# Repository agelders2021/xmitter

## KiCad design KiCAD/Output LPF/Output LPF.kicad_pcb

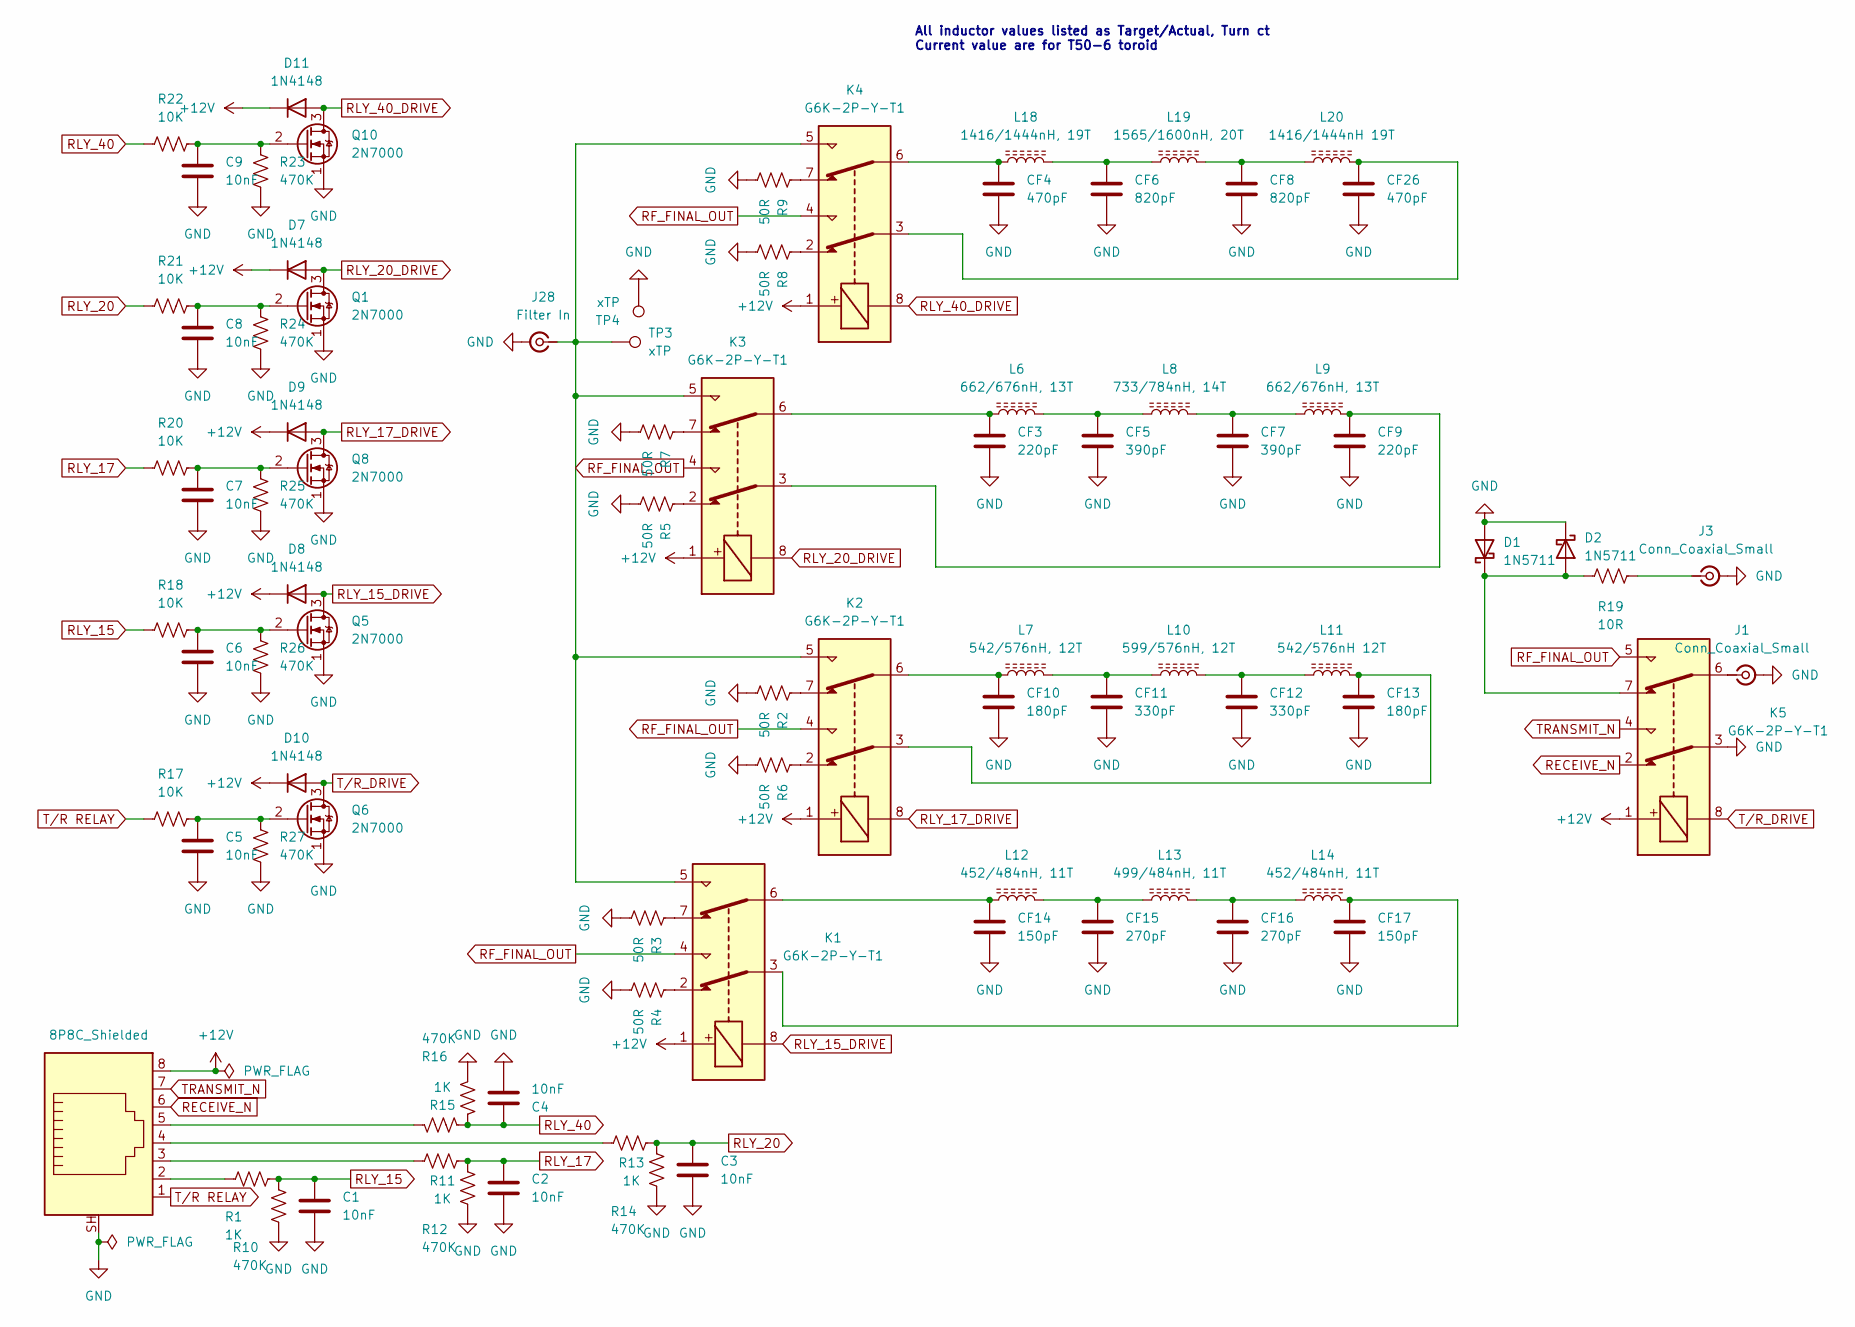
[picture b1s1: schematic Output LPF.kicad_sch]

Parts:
C1, C2, C3, C4, C5, C6, C7, C8, C9: 10nF; C_Disc_D6.0mm_W2.5mm_P5.00mm
CF3, CF9: 220pF; C_Disc_D7.5mm_W2.5mm_P5.00mm; Tolerance 1%
CF4, CF26: 470pF; C_Disc_D7.5mm_W2.5mm_P5.00mm; Tolerance 1%
CF5, CF7: 390pF; C_Disc_D7.5mm_W2.5mm_P5.00mm; Tolerance 1%
CF6, CF8: 820pF; C_Disc_D7.5mm_W2.5mm_P5.00mm; Tolerance 1%
CF10, CF13: 180pF; C_Disc_D7.5mm_W2.5mm_P5.00mm; Tolerance 1%
CF11, CF12: 330pF; C_Disc_D7.5mm_W2.5mm_P5.00mm; Tolerance 1%
CF14, CF17: 150pF; C_Disc_D7.5mm_W2.5mm_P5.00mm; Tolerance 1%
CF15, CF16: 270pF; C_Disc_D7.5mm_W2.5mm_P5.00mm; Tolerance 1%
D1, D2: 1N5711; D_DO-35_SOD27_P7.62mm_Horizontal
D7, D8, D9, D10, D11: 1N4148; D_DO-35_SOD27_P7.62mm_Horizontal
J1, J3: Conn_Coaxial_Small; SMA_Amphenol_132134_Vertical
J2: 8P8C_Shielded; Amphenol_RJE1D-188_Horizontal_Shielded
J28: Filter In; SMA_Amphenol_132134_Vertical
K1, K2, K3, K4, K5: G6K-2P-Y-T1; Relay_DPDT_G6K-2P-Y-T1
L6, L9: 662/676nH, 13T; T50-6_Vertical_HandWound
L7: 542/576nH, 12T; T50-6_Flat_HandWound
L8: 733/784nH, 14T; T50-6_Flat_HandWound
L10: 599/576nH, 12T; T50-6_Vertical_HandWound
L11: 542/576nH 12T; T50-6_Flat_HandWound
L12, L14: 452/484nH, 11T; T50-6_Flat_HandWound
L13: 499/484nH, 11T; T50-6_Vertical_HandWound
L18: 1416/1444nH, 19T; T50-6_Vertical_HandWound
L19: 1565/1600nH, 20T; T50-6_Flat_HandWound
L20: 1416/1444nH 19T; T50-6_Vertical_HandWound
Q1, Q5, Q6, Q8, Q10: 2N7000; TO-92_Inline
R1, R11, R13, R15: 1K; R_Axial_DIN0207_L6.3mm_D2.5mm_P10.16mm_Horizontal
R2, R3, R4, R5, R6, R7, R8, R9: 50R; R_Axial_DIN0207_L6.3mm_D2.5mm_P10.16mm_Horizontal
R10, R12, R14, R16, R23, R24, R25, R26, R27: 470K; R_Axial_DIN0207_L6.3mm_D2.5mm_P10.16mm_Horizontal
R17, R18, R20, R21, R22: 10K; R_Axial_DIN0207_L6.3mm_D2.5mm_P10.16mm_Horizontal
R19: 10R; R_Axial_DIN0207_L6.3mm_D2.5mm_P10.16mm_Horizontal
TP3, TP4: xTP; PinHeader_1x01_P2.54mm_Vertical

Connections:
+12V: D7.1 (K), D8.1 (K), D9.1 (K), D10.1 (K), D11.1 (K), J2.8, K1.1, K2.1, K3.1, K4.1, K5.1
GND: C1.2, C2.2, C3.2, C4.2, C5.2, C6.2, C7.2, C8.2, C9.2, CF3.2, CF4.2, CF5.2, CF6.2, CF7.2, CF8.2, CF9.2, CF10.2, CF11.2, CF12.2, CF13.2, CF14.2, CF15.2, CF16.2, CF17.2, CF26.2, D1.2 (A), D2.1 (K), J1.2 (Ext), J2.SH, J3.2 (Ext), J28.2 (Ext), K5.3, Q1.1 (S), Q5.1 (S), Q6.1 (S), Q8.1 (S), Q10.1 (S), R2.2, R3.2, R4.2, R5.2, R6.2, R7.2, R8.2, R9.2, R10.2, R12.2, R14.2, R16.2, R23.2, R24.2, R25.2, R26.2, R27.2, TP4.1 (1_1)
unnamed: CF3.1, K3.6, L6.1
unnamed: CF4.1, K4.6, L18.1
unnamed: CF5.1, L6.2, L8.1
unnamed: CF6.1, L18.2, L19.1
unnamed: CF7.1, L8.2, L9.1
unnamed: CF8.1, L19.2, L20.1
unnamed: CF9.1, K3.3, L9.2
unnamed: CF10.1, K2.6, L7.1
unnamed: CF11.1, L7.2, L10.1
unnamed: CF12.1, L10.2, L11.1
unnamed: CF13.1, K2.3, L11.2
unnamed: CF14.1, K1.6, L12.1
unnamed: CF15.1, L12.2, L13.1
unnamed: CF16.1, L13.2, L14.1
unnamed: CF17.1, K1.3, L14.2
unnamed: CF26.1, K4.3, L20.2
unnamed: D1.1 (K), D2.2 (A), K5.7, R19.1
unnamed: J1.1 (In), K5.6
unnamed: J2.2, R1.1
unnamed: J2.3, R11.1
unnamed: J2.4, R13.1
unnamed: J2.5, R15.1
unnamed: J3.1 (In), R19.2
unnamed: J28.1 (In), K1.5, K2.5, K3.5, K4.5, TP3.1 (1_1)
unnamed: K1.2, R4.1
unnamed: K1.7, R3.1
unnamed: K2.2, R6.1
unnamed: K2.7, R2.1
unnamed: K3.2, R5.1
unnamed: K3.7, R7.1
unnamed: K4.2, R8.1
unnamed: K4.7, R9.1
unnamed: C8.1, Q1.2 (G), R21.2, R24.1
unnamed: C6.1, Q5.2 (G), R18.2, R26.1
unnamed: C5.1, Q6.2 (G), R17.2, R27.1
unnamed: C7.1, Q8.2 (G), R20.2, R25.1
unnamed: C9.1, Q10.2 (G), R22.2, R23.1
RECEIVE_N: J2.6, K5.2
RF_FINAL_OUT: K1.4, K2.4, K3.4, K4.4, K5.5
RLY_15: C1.1, R1.2, R10.1, R18.1
RLY_15_DRIVE: D8.2 (A), K1.8, Q5.3 (D)
RLY_17: C2.1, R11.2, R12.1, R20.1
RLY_17_DRIVE: D9.2 (A), K2.8, Q8.3 (D)
RLY_20: C3.1, R13.2, R14.1, R21.1
RLY_20_DRIVE: D7.2 (A), K3.8, Q1.3 (D)
RLY_40: C4.1, R15.2, R16.1, R22.1
RLY_40_DRIVE: D11.2 (A), K4.8, Q10.3 (D)
TRANSMIT_N: J2.7, K5.4
T/R RELAY: J2.1, R17.1
T/R_DRIVE: D10.2 (A), K5.8, Q6.3 (D)

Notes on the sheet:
All inductor values listed as Target/Actual, Turn ct Current value are for T50-6 toroid

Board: 2 copper layers, 87 parts (0 on the bottom side), 52 nets, no tracks yet.

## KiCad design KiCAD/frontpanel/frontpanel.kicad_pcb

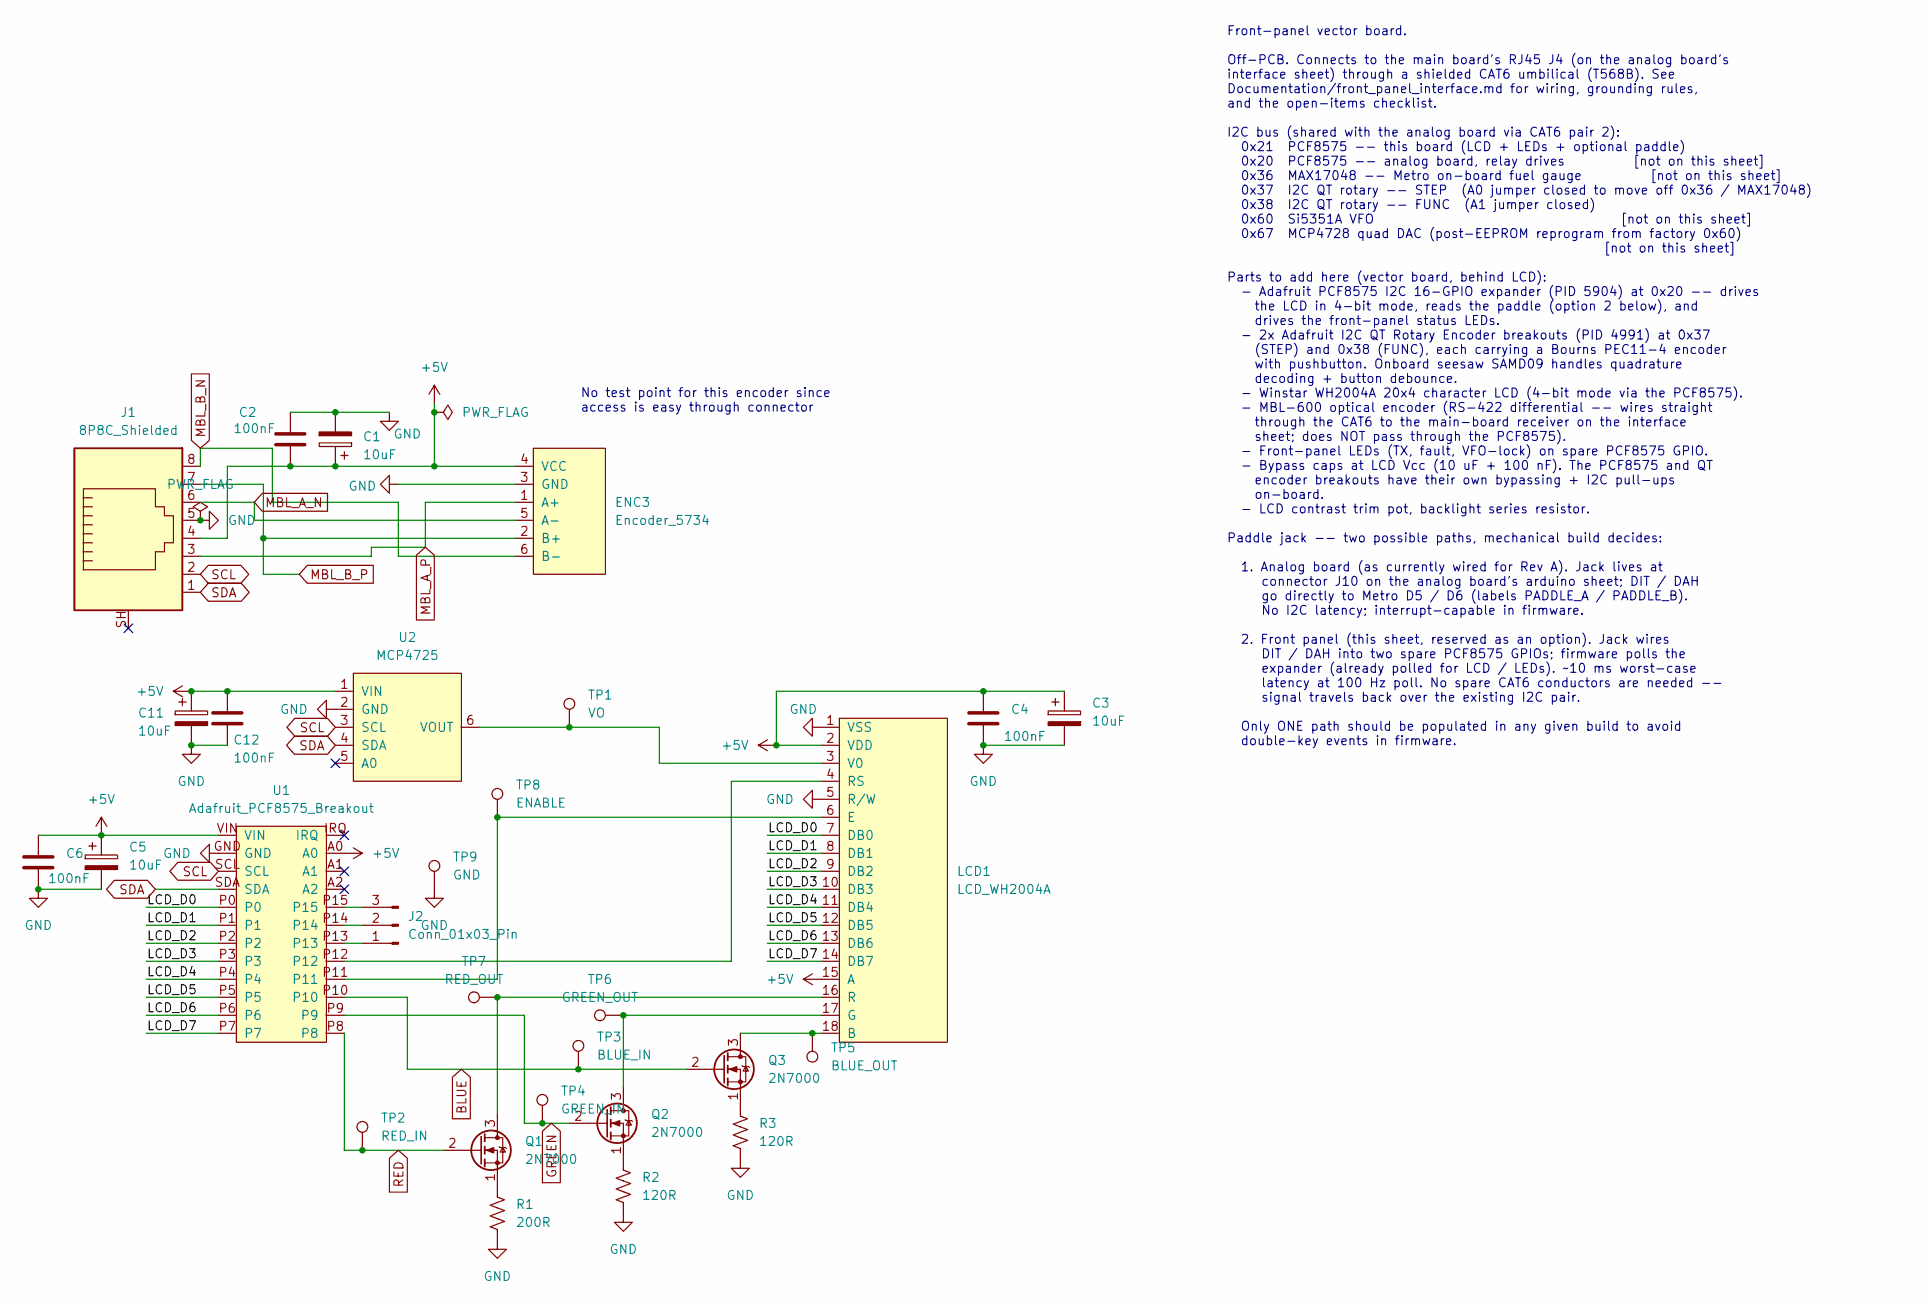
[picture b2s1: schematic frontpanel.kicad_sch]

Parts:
C1, C3, C5, C11: 10uF; CP_Radial_D5.0mm_P2.00mm
C2, C4, C6, C12: 100nF; C_Disc_D5.0mm_W2.5mm_P5.00mm
ENC3: Encoder_5734; PinHeader_1x06_P2.54mm_Vertical; MPN Adafruit #5734
J1: 8P8C_Shielded; Amphenol_RJE1D-188_Horizontal_Shielded
J2: Conn_01x03_Pin; PinHeader_1x03_P2.54mm_Vertical
LCD1: LCD_WH2004A; PinHeader_1x18_P2.54mm_Vertical; MPN WH2004A-CFH-JT# / Adafruit #498
Q1, Q2, Q3: 2N7000; TO-92_Inline
R1: 200R; R_Axial_DIN0207_L6.3mm_D2.5mm_P10.16mm_Horizontal
R2, R3: 120R; R_Axial_DIN0207_L6.3mm_D2.5mm_P10.16mm_Horizontal
TP1: VO; PinHeader_1x01_P2.54mm_Vertical
TP2: RED_IN; PinHeader_1x01_P2.54mm_Vertical
TP3: BLUE_IN; PinHeader_1x01_P2.54mm_Vertical
TP4: GREEN_IN; PinHeader_1x01_P2.54mm_Vertical
TP5: BLUE_OUT; PinHeader_1x01_P2.54mm_Vertical
TP6: GREEN_OUT; PinHeader_1x01_P2.54mm_Vertical
TP7: RED_OUT; PinHeader_1x01_P2.54mm_Vertical
TP8: ENABLE; PinHeader_1x01_P2.54mm_Vertical
TP9: GND; PinHeader_1x01_P2.54mm_Vertical
U1: Adafruit_PCF8575_Breakout; MPN Adafruit #5904
U2: MCP4725; Adafruit_MCP4725_Breakout; MPN Adafruit #935

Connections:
+5V: C1.1, C2.2, C3.1, C4.1, C5.1, C6.1, C11.1, C12.1, ENC3.4 (VCC), J1.4, LCD1.2 (VDD), LCD1.15 (A), U1.A0, U1.VIN, U2.1 (VIN)
/LCD_D0: LCD1.7 (DB0), U1.P0
/LCD_D1: LCD1.8 (DB1), U1.P1
/LCD_D2: LCD1.9 (DB2), U1.P2
/LCD_D3: LCD1.10 (DB3), U1.P3
/LCD_D4: LCD1.11 (DB4), U1.P4
/LCD_D5: LCD1.12 (DB5), U1.P5
/LCD_D6: LCD1.13 (DB6), U1.P6
/LCD_D7: LCD1.14 (DB7), U1.P7
BLUE: Q3.2 (G), TP3.1 (1_1), U1.P10
GND: C1.2, C2.1, C3.2, C4.2, C5.2, C6.2, C11.2, C12.2, ENC3.3 (GND), J1.5, LCD1.1 (VSS), LCD1.5 (R/W), R1.2, R2.2, R3.2, TP9.1 (1_1), U1.GND, U2.2 (GND)
GREEN: Q2.2 (G), TP4.1 (1_1), U1.P9
MBL_A_N: ENC3.5 (A-), J1.6
MBL_A_P: ENC3.1 (A+), J1.3
MBL_B_N: ENC3.6 (B-), J1.8
MBL_B_P: ENC3.2 (B+), J1.7
unnamed: J2.1, U1.P13
unnamed: J2.2, U1.P14
unnamed: J2.3, U1.P15
unnamed: LCD1.18 (B), Q3.3 (D), TP5.1 (1_1)
unnamed: LCD1.6 (E), TP8.1 (1_1), U1.P11
unnamed: LCD1.17 (G), Q2.3 (D), TP6.1 (1_1)
unnamed: LCD1.16 (R), Q1.3 (D), TP7.1 (1_1)
unnamed: LCD1.4 (RS), U1.P12
unnamed: LCD1.3 (V0), TP1.1 (1_1), U2.6 (VOUT)
unnamed: Q1.1 (S), R1.1
unnamed: Q2.1 (S), R2.1
unnamed: Q3.1 (S), R3.1
RED: Q1.2 (G), TP2.1 (1_1), U1.P8
SCL: J1.2, U1.SCL, U2.3 (SCL)
SDA: J1.1, U1.SDA, U2.4 (SDA)

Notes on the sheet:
Front-panel vector board. Off-PCB. Connects to the main board's RJ45 J4 (on the analog board's interface sheet) through a shielded CAT6 umbilical (T568B). See Documentation/front_panel_interface.md for wiring, grounding rules, and the open-items checklist. I2C bus (shared with the analog board via 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
No test point for this encoder since access is easy through connector

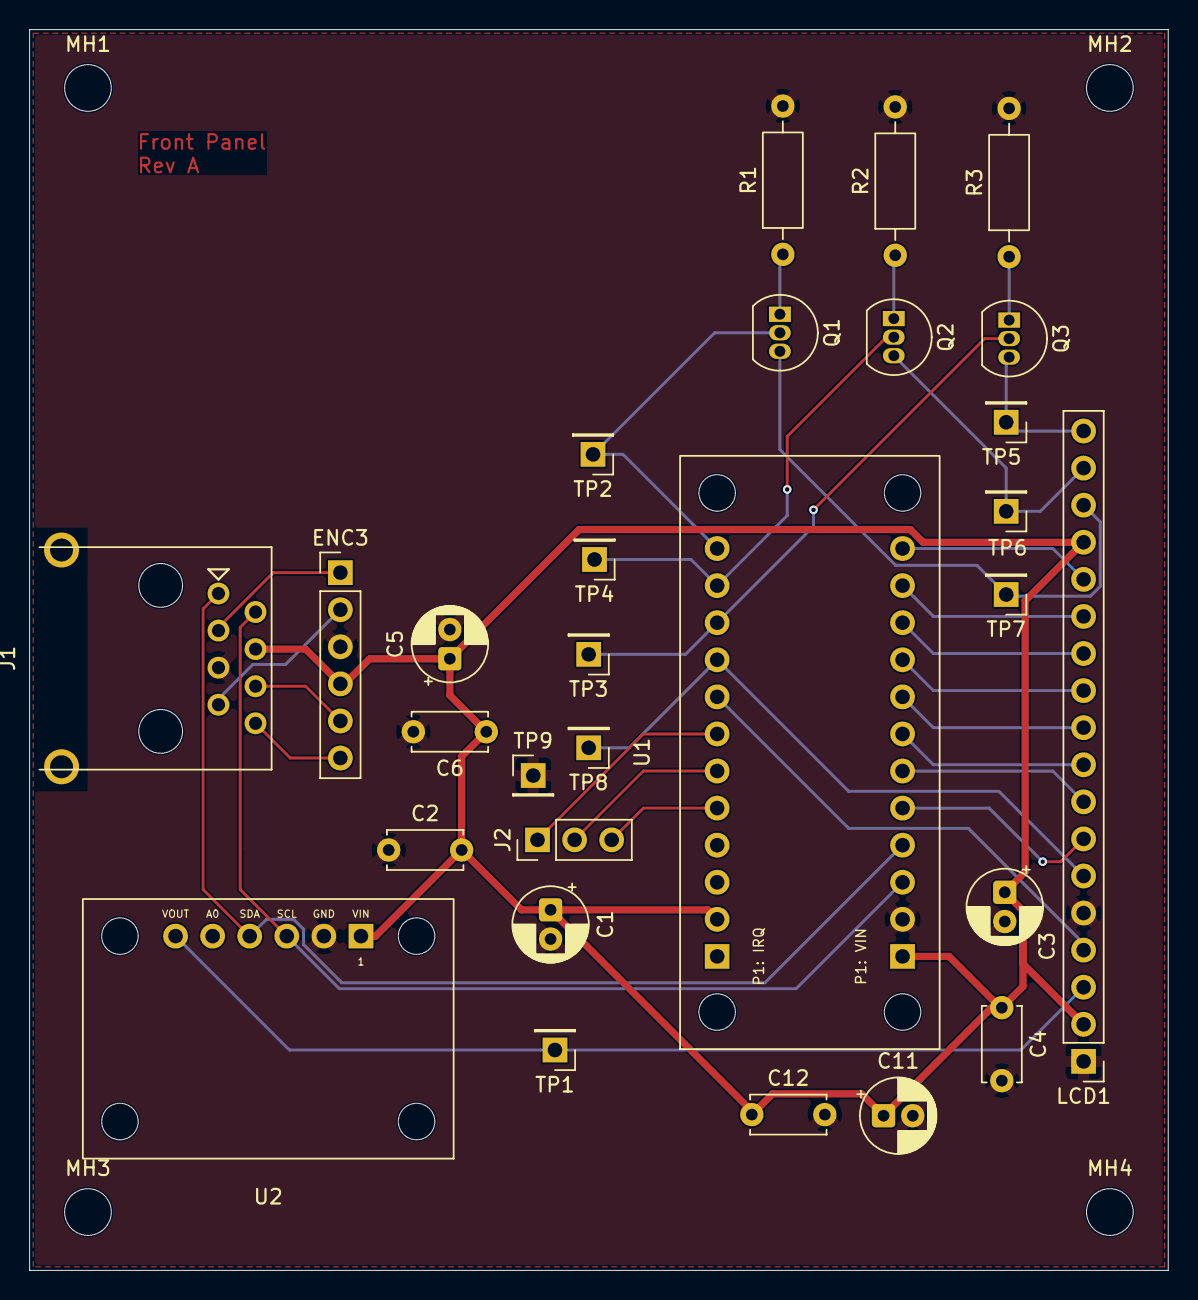
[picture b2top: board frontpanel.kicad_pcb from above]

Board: 2 copper layers, 78.0 x 85.0 mm, 33 parts (0 on the bottom side), 31 nets.

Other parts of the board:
MH1, MH2, MH3, MH4: MountingHole_3.2mm_M3

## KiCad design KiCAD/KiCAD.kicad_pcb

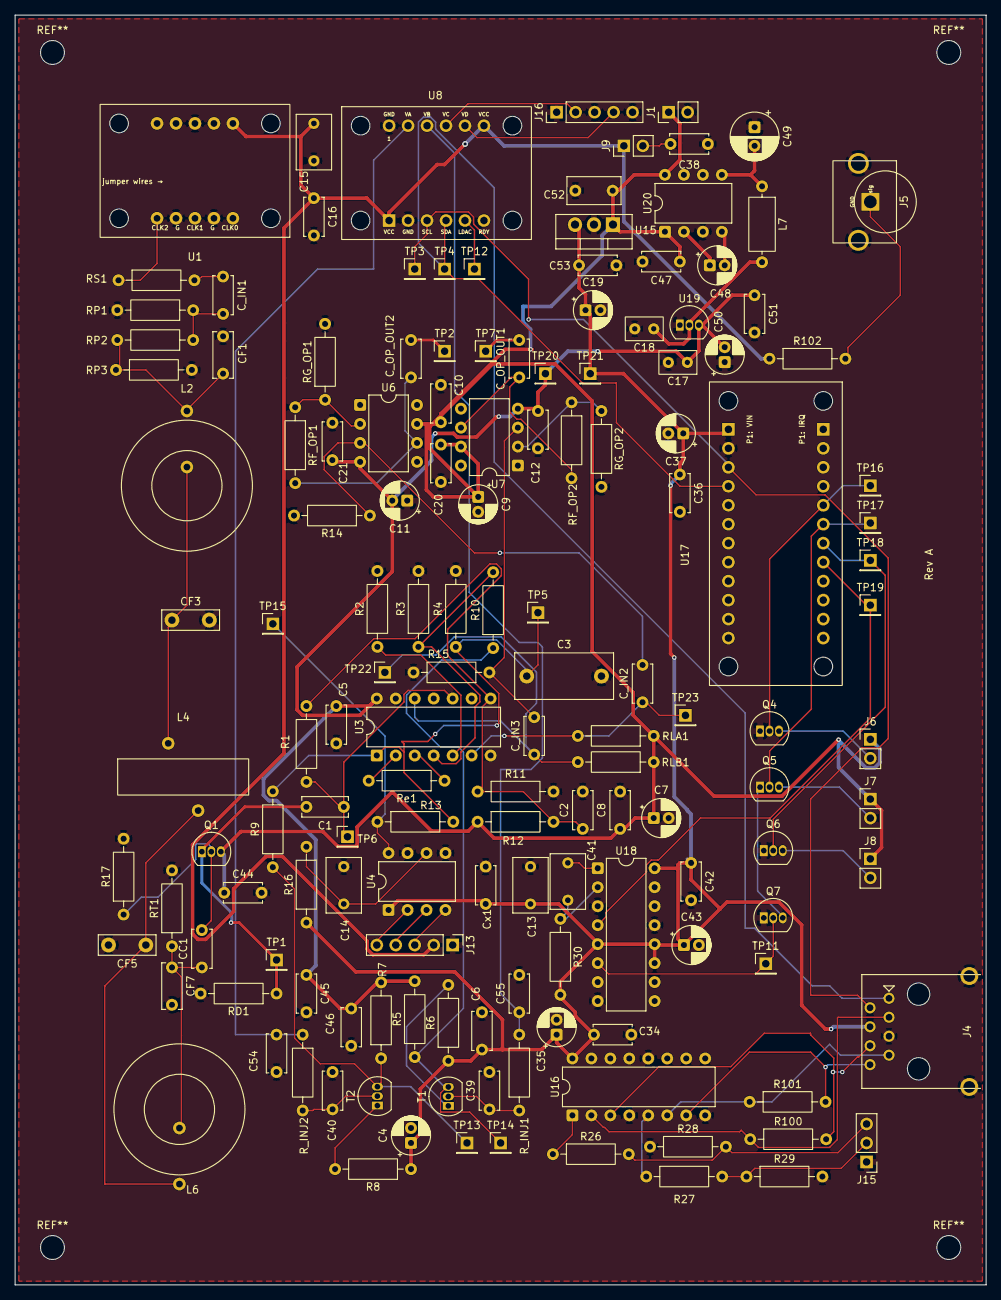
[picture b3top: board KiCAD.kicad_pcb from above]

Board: 2 copper layers, 130.0 x 170.0 mm, 147 parts (0 on the bottom side), 74 nets.

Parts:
C1: 330pF; C_Disc_D6.0mm_W2.5mm_P5.00mm
C2, C5, C6, C8, C10, C12, C16, C20, C21, C34, C36, C38, C39, C40, C42, C44, C45, C46, C51, C54, C55: 100nF; C_Disc_D5.0mm_W2.5mm_P5.00mm
C3: 680nF; C_Rect_L13.0mm_W6.0mm_P10.00mm_FKS3_FKP3_MKS4
C4, C7, C9, C11, C19, C35, C37, C43, C48, C50: 10uF; CP_Radial_D5.0mm_P2.00mm
C13, C14, C15, C41: 1uF; C_Rect_L7.2mm_W4.5mm_P5.00mm
C17, C18: 0.33uF; Kyocera_SR20_MLCC
C47, C53: 0.1uF; C_Disc_D5.0mm_W2.5mm_P5.00mm
C49: 100uF; CP_Radial_D6.3mm_P2.50mm
C52: 0.33uF; C_Rect_L7.0mm_W3.5mm_P5.00mm
CC1: 10nF; C_Disc_D5.0mm_W2.5mm_P5.00mm
CF1, CF7: 220pF; C_Disc_D6.0mm_W2.5mm_P5.00mm
CF3, CF5: 390pF; C_Disc_D7.5mm_W2.5mm_P5.00mm
C_IN1: 10nF; C_Disc_D5.0mm_W2.5mm_P5.00mm
C_IN2, C_IN3: 100nF; C_Disc_D5.0mm_W2.5mm_P5.00mm
C_OP_OUT1, C_OP_OUT2: 100nF; C_Disc_D5.0mm_W2.5mm_P5.00mm
Cx1: 100nF; C_Disc_D5.0mm_W2.5mm_P5.00mm
J1: Conn_01x02_Pin; PinHeader_1x02_P2.54mm_Vertical
J4: 8P8C_Shielded; Amphenol_RJE1D-188_Horizontal_Shielded
J5: ENC_INT if needed; SameSky_RCJ-02_RCA_Jack
J6: TX/RX; PinHeader_1x02_P2.54mm_Vertical
J7: HV; PinHeader_1x02_P2.54mm_Vertical
J8: HV_INRUSH_BYPASS; PinHeader_1x02_P2.54mm_Vertical
J9: TR_SENSE; PinHeader_1x02_P2.54mm_Vertical
J13, J16: Conn_01x05; PinHeader_1x05_P2.54mm_Vertical
J15: Conn_01x03_Pin; PinHeader_1x03_P2.54mm_Vertical
L2, L6: 736nH; T68-6_Flat_HandWound
L4: 736nH; T68-6_Vertical_HandWound
L7: 22uH; L_Axial_L7.0mm_D3.3mm_P10.16mm_Horizontal_Fastron_MICC
Q1: J310; TO-92_Inline
Q4, Q5, Q6, Q7: 2N7000; TO-92_Inline
R1, R3, R4: 51R; R_Axial_DIN0207_L6.3mm_D2.5mm_P10.16mm_Horizontal
R2: 6K8; R_Axial_DIN0207_L6.3mm_D2.5mm_P10.16mm_Horizontal
R5, R7, R9, R10: 8K2; R_Axial_DIN0207_L6.3mm_D2.5mm_P10.16mm_Horizontal
R6, R8: 2K7; R_Axial_DIN0207_L6.3mm_D2.5mm_P10.16mm_Horizontal
R11, R12: 22K; R_Axial_DIN0207_L6.3mm_D2.5mm_P10.16mm_Horizontal
R13: 1K5; R_Axial_DIN0207_L6.3mm_D2.5mm_P10.16mm_Horizontal
R14, R15: 100K; R_Axial_DIN0207_L6.3mm_D2.5mm_P10.16mm_Horizontal
R16: 10R; R_Axial_DIN0207_L6.3mm_D2.5mm_P10.16mm_Horizontal
R17, R28, R29, R102: 10K; R_Axial_DIN0207_L6.3mm_D2.5mm_P10.16mm_Horizontal
R26, R27: 2.2K; R_Axial_DIN0207_L6.3mm_D2.5mm_P10.16mm_Horizontal
R30: 470K; R_Axial_DIN0207_L6.3mm_D2.5mm_P10.16mm_Horizontal
R100, R101: 120; R_Axial_DIN0207_L6.3mm_D2.5mm_P10.16mm_Horizontal
RD1: 270R; R_Axial_DIN0207_L6.3mm_D2.5mm_P10.16mm_Horizontal
RF_OP1, RF_OP2: 30K; R_Axial_DIN0207_L6.3mm_D2.5mm_P10.16mm_Horizontal
RG_OP1, RG_OP2: 10K; R_Axial_DIN0207_L6.3mm_D2.5mm_P10.16mm_Horizontal
RLA1: 3K9; R_Axial_DIN0207_L6.3mm_D2.5mm_P10.16mm_Horizontal
RLB1: 3K9; R_Axial_DIN0207_L6.3mm_D2.5mm_P10.16mm_Horizontal
RP1, RP3: 62R; R_Axial_DIN0207_L6.3mm_D2.5mm_P10.16mm_Horizontal
RP2: 240R; R_Axial_DIN0207_L6.3mm_D2.5mm_P10.16mm_Horizontal
RS1: 0R; R_Axial_DIN0207_L6.3mm_D2.5mm_P10.16mm_Horizontal
RT1: 50R; R_Axial_DIN0207_L6.3mm_D2.5mm_P10.16mm_Horizontal
R_INJ1, R_INJ2: 330K; R_Axial_DIN0207_L6.3mm_D2.5mm_P10.16mm_Horizontal
Re1: 2K; R_Axial_DIN0207_L6.3mm_D2.5mm_P10.16mm_Horizontal
T1, T2: 2N3906; TO-92_Inline
TP1: RAW_RF; PinHeader_1x01_P2.54mm_Vertical
TP2: MOD_RF+; PinHeader_1x01_P2.54mm_Vertical
TP3: SCL; PinHeader_1x01_P2.54mm_Vertical
TP4: SDA; PinHeader_1x01_P2.54mm_Vertical
TP5: KEY_SIG; PinHeader_1x01_P2.54mm_Vertical
TP6: CARRIER_IN; PinHeader_1x01_P2.54mm_Vertical
TP7: MOD_RF-; PinHeader_1x01_P2.54mm_Vertical
TP11: Heartbeat; PinHeader_1x01_P2.54mm_Vertical
TP12: LDAC; PinHeader_1x01_P2.54mm_Vertical
TP13: T2 out; PinHeader_1x01_P2.54mm_Vertical
TP14: T1 out; PinHeader_1x01_P2.54mm_Vertical
TP15: Key_Out; PinHeader_1x01_P2.54mm_Vertical
TP16: TX/RX; PinHeader_1x01_P2.54mm_Vertical
TP17: HV; PinHeader_1x01_P2.54mm_Vertical
TP18: Inrush; PinHeader_1x01_P2.54mm_Vertical
TP19: HB trigger; PinHeader_1x01_P2.54mm_Vertical
TP20: VEE; PinHeader_1x01_P2.54mm_Vertical
TP21: +5V; PinHeader_1x01_P2.54mm_Vertical
TP22: OUT-; PinHeader_1x01_P2.54mm_Vertical
TP23: OUT+; PinHeader_1x01_P2.54mm_Vertical
U1: Si5351A_Breakout; Adafruit_Si5351A_STEMMA
U3: MC1496; DIP-14_W7.62mm
U4: MCP4921; DIP-8_W7.62mm
U6, U7: LM7171xIN; DIP-8_W7.62mm
U8: MCP4728; Adafruit_MCP4728_Breakout
U15: LM7805_TO220; TO-220-3_Vertical
U16: AM26LS32ACN; DIP-16_W7.62mm
U17: Adafruit_PCF8575_Breakout
U18: CD14538B; DIP-16_W7.62mm
U19: L79L08_TO92; TO-92_Inline
U20: ICL7660S; DIP-8_W7.62mm

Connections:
3V3: C15.1, C16.1, J9.1, J13.2, R102.1, U1.VIN, U8.1 (VIN)
+5V: C4.1, C6.1, C13.1, C19.1, C34.1, C35.1, C36.1, C37.1, C42.1, C43.1, C53.1, Cx1.2, J4.4, R6.1, R8.1, R16.1, R30.2, TP21.1 (1_1), U4.1 (VDD), U15.3 (VO), U16.16 (VCC), U17.VIN, U18.5 (~RST_A), U18.11 (~RST_B), U18.12 (+TR_B), U18.16 (VDD)
+12V: C7.1, C8.1, C9.1, C10.1, C20.1, C44.1, C47.1, C52.1, J1.1, J6.1, J7.1, J8.1, Q1.3 (D), R12.1, RLA1.1, RLB1.1, U6.7 (V+), U7.7 (V+), U15.1 (VI), U20.1 (BOOST), U20.8 (V+)
CS_DAC: J13.5, U4.2 (~CS)
DRV_OUT+: C_OP_OUT2.1, RF_OP1.2, U6.6
DRV_OUT-: C_OP_OUT1.1, RF_OP2.2, U7.6
GND: C2.2, C3.2, C4.2, C5.2, C6.2, C7.2, C8.2, C9.2, C10.2, C11.1, C12.1, C13.2, C14.1, C15.2, C16.2, C17.2, C18.2, C19.2, C20.2, C21.1, C34.2, C35.2, C36.2, C37.2, C38.2, C39.2, C40.2, C42.2, C43.2, C44.2, C45.2, C46.2, C47.2, C49.1, C50.1, C51.2, C52.2, C53.2, C54.2, C55.2, CF1.2, CF3.2, CF5.2, CF7.2, Cx1.1, J1.2, J4.5, J4.SH, J5.2 (Ext), J13.1, J15.1, J16.1, J16.3, J16.5, Q4.1 (S), Q6.1 (S), Q7.1 (S), R2.2, R3.2, R4.2, R11.2, R14.2, R15.2, R17.2, R28.1, R29.2, RD1.2, RG_OP1.2, RG_OP2.2, RP1.2, RP3.2, RT1.2, U1.GND, U4.5 (~LDAC), U4.7 (VSS), U8.2 (GND), U15.2 (GND), U16.4 (~EN12), U16.8 (GND), U16.12 (EN34), U17.GND, U18.3 (-TR_A), U18.8 (VSS), U18.13 (-TR_B), U19.1 (GND), U20.3 (GND)
GRID_CTL_A: J16.2, U8.9 (VC)
GRID_CTL_B: J16.4, U8.10 (VD)
LDAC_4728: TP12.1 (1_1), U8.5 (LDAC)
MBL600_A: J15.3, R26.2, R28.2
MBL600_B: J15.2, R27.2, R29.1
MBL_A_N: J4.6, R100.2, U16.3 (1B)
MBL_A_P: J4.3, R100.1, U16.2 (1A)
MBL_B_N: J4.8, R101.2, U16.7 (2B)
MBL_B_P: J4.7, R101.1, U16.6 (2A)
MC_OUT+: C_IN2.1, RLA1.2, TP23.1 (1_1), U3.6 (OUT+)
MC_OUT-: C_IN3.1, RLB1.2, TP22.1 (1_1), U3.12 (OUT-)
MOD_RF_OUT+: C_OP_OUT2.2, TP2.1 (1_1)
MOD_RF_OUT-: C_OP_OUT1.2, TP7.1 (1_1)
MOSI: J13.3, U4.4 (SDI)
unnamed: CC1.1, CF7.1, L6.2, RT1.1
unnamed: CF1.1, L2.1, RP2.2, RP3.1
unnamed: CF3.1, L2.2, L4.1
unnamed: CF5.1, L4.2, L6.1
unnamed: C_IN1.1, RS1.2
unnamed: C_IN1.2, RP1.1, RP2.1
unnamed: J5.1 (In), R102.2
unnamed: J6.2, Q4.3 (D)
unnamed: J7.2, Q5.3 (D)
unnamed: J8.2, Q6.3 (D)
unnamed: C38.1, J9.2
unnamed: CC1.2, Q1.2 (G), R17.1
unnamed: Q4.2 (G), TP16.1 (1_1), U17.P15
unnamed: Q5.2 (G), TP17.1 (1_1), U17.P14
unnamed: Q5.1 (S), Q7.3 (D)
unnamed: Q6.2 (G), TP18.1 (1_1), U17.P13
unnamed: Q7.2 (G), TP11.1 (1_1), U18.6 (Q_A)
unnamed: RS1.1, U1.CLK2
unnamed: C39.1, R_INJ1.1, T1.2 (B)
unnamed: R6.2, T1.1 (E)
unnamed: C40.1, R_INJ2.2, T2.2 (B)
unnamed: R8.2, T2.1 (E)
unnamed: R2.1, U3.5 (BIAS)
unnamed: C1.1, R1.2, TP6.1 (1_1), U3.10 (CAR_IN+)
unnamed: C2.1, R1.1, R11.1, R12.2, U3.8 (CAR_IN-)
unnamed: Re1.2, U3.2 (GADJ_A)
unnamed: Re1.1, U3.3 (GADJ_B)
unnamed: C3.1, R4.1, R9.2, R13.2, TP5.1 (1_1), U3.1 (SIG_IN+)
unnamed: R3.1, R10.2, U3.4 (SIG_IN-)
unnamed: R13.1, TP15.1 (1_1), U4.8 (VOUT)
unnamed: C14.2, R16.2, U4.6 (VREF)
unnamed: C_IN2.2, R14.1, U6.3 (+)
unnamed: RF_OP1.1, RG_OP1.1, U6.2 (-)
unnamed: C_IN3.2, R15.1, U7.3 (+)
unnamed: RF_OP2.1, RG_OP2.1, U7.2 (-)
unnamed: R26.1, U16.1 (1Y)
unnamed: R27.1, U16.5 (2Y)
unnamed: TP19.1 (1_1), U17.P12, U18.4 (+TR_A)
unnamed: C41.1, U18.1 (C_A)
unnamed: C41.2, R30.1, U18.2 (RC_A)
unnamed: C18.1, L7.2, U19.2 (VI)
unnamed: C48.1, U20.2 (CAP+)
unnamed: C48.2, U20.4 (CAP-)
unnamed: C49.2, L7.1, U20.5 (VOUT)
RAW_RF: C1.2, Q1.1 (S), RD1.1, TP1.1 (1_1)
SCK: J13.4, U4.3 (SCK)
SCL: J4.2, TP3.1 (1_1), U8.3 (SCL), U17.SCL
SDA: J4.1, TP4.1 (1_1), U8.4 (SDA), U17.SDA
T1_COL: R5.1, R10.1, T1.3 (C), TP14.1 (1_1)
T2_COL: R7.1, R9.1, T2.3 (C), TP13.1 (1_1)
VA_INJ: C54.1, R_INJ2.1, U8.7 (VA)
VB_INJ: C55.1, R_INJ1.2, U8.8 (VB)
VEE: C5.1, C11.2, C12.2, C17.1, C21.2, C45.1, C46.1, C50.2, C51.1, R5.2, R7.2, TP20.1 (1_1), U3.14 (VEE), U6.4 (V-), U7.4 (V-), U19.3 (VO)

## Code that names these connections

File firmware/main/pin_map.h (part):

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constexpr spi_host_device_t DAC_SPI_HOST = SPI2_HOST;     // = FSPI
constexpr gpio_num_t        ENV_DAC_SCK  = GPIO_NUM_13;   // Arduino D13 (SCK)
constexpr gpio_num_t        ENV_DAC_MOSI = GPIO_NUM_11;   // Arduino D11 (MOSI)
constexpr gpio_num_t        ENV_DAC_CS   = GPIO_NUM_10;   // Arduino D10 (CS_DAC)
constexpr int               ENV_DAC_HZ   = 20000000;      // MCP4921 max ~20 MHz

// ---------------------------------------------------------------------------
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//  quadrature decode + button debounce on-board).  They are on the I2C
//  bus at ENC_STEP / ENC_FUNC addresses above — no dedicated GPIOs.
// ---------------------------------------------------------------------------
constexpr gpio_num_t ENC_FREQ_A    = GPIO_NUM_2;    // Arduino D2 (MBL600_A)
constexpr gpio_num_t ENC_FREQ_B    = GPIO_NUM_3;    // Arduino D3 (MBL600_B)
constexpr gpio_num_t ENC_FREQ_SW   = GPIO_NUM_NC;   // optical encoder has no switch

// STEP / FUNC now live on I2C QT breakouts.  These constants are kept as
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//  Metro-pin usage on the Rev A analog control board (arduino.kicad_sch):
//    D0  = GPIO41  — RX (unused; UART debug runs on GPIO44)
//    D1  = GPIO40  — TX (unused)
//    D2  = GPIO2   — MBL600_A       (VFO tuning encoder, quadrature A)
//    D3  = GPIO3   — MBL600_B       (VFO tuning encoder, quadrature B)
//    D4  = GPIO4   — ENC_INT (reserved for future front-panel INT cable;
//                    J5 header unpopulated on Rev A build)
//    D5  = GPIO5   — PADDLE_A / DIT
//    D6  = GPIO6   — PADDLE_B / DAH
//    D7  = GPIO7   — LDAC_4728      (MCP4728 EEPROM reprogram; see above)
//    D8  = GPIO8   — I_CATHODE_A    (per-tube cathode current, ADC1)
//    D9  = GPIO9   — I_CATHODE_B    (per-tube cathode current, ADC1)
//    D10 = GPIO10  — CS_DAC         (SPI CS for envelope MCP4921)
//    D11 = GPIO11  — MOSI           (envelope DAC MOSI)
//    D12 = GPIO12  — ADC2           (spare analog input)
//    D13 = GPIO13  — SCK            (envelope DAC clock)
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
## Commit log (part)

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2026-06-07 Work in Progress
2026-06-19 kicad: control-board sheets — buffer_keyer keyer body, arduino SPI labels, custom-symbol plan
    - buffer_keyer.kicad_sch: place MC1496 keyer support components
    (carrier divider R11/R12, modulator port R3, emitter-degen Re,
    modulator coupling C1, VEE bypass C5, R2 Iee, bypass network),
    MCP4921 envelope DAC U4 with reconstruction cap C3, terminal
    blocks J1/J2/J3 for +5V/+12V/-90V/VEE input, hierarchical labels
    for VFO_OUT, SCK, MOSI, CS_DAC.
2026-06-19 kicad: redesign Metro_ESP32S3 as wide 25-pin xmitter symbol + wire arduino sheet
    - xmitter.kicad_sym: replace Metro_ESP32S3 with a 25-pin compact symbol
    (was 34-pin stock with cluttered alt-function labels). Body 25.4 x
    34.3 mm. 19 active pins (power, control, UART, I2C, SPI, paddle,
    TX_LED) + 6 analog spares (A0-A5) for future expansion.
    - arduino.kicad_sch: cached lib_symbols mirrors the new definition; wire
    Metro pins to hierarchical labels (SDA, SCL, SCK, MOSI, CS_DAC, 3V3)
2026-06-19 kicad + docs: add MCP4728 (null DAC) symbol, document I2C address-conflict resolution and PCB-trace routing decision
    Hardware change: Adafruit MCP4728 4-channel I2C DAC (PID 4470) on hand,
    intended for the dual-channel digital carrier-null feature previously
    labeled "designed but not built" in cw_envelope_keyer.md.
    - xmitter.kicad_sym: new xmitter:MCP4728 symbol — 10 pins matching the
    Adafruit breakout's 0.1" header (VIN, GND, SCL, SDA, LDAC, RDY, VA-VD).
    Built via tools/add_mcp4728_symbol.py (declarative pin list, same
2026-06-20 docs(keyer): correct null-injection topology to match QUCS sim and MC1496 app note
    The "Future enhancement: DAC-driven digital carrier null" section of
    cw_envelope_keyer.md described "330 kohm direct injection at MC1496
    pins 1/4 (SIG_P, SIG_N)". That description was wrong on two counts:
    1. It contradicts what xmitter_prj/keyer.sch actually simulates. In the
    QUCS schematic, the DAC1/DAC2 ports tie DIRECTLY to T1/T2 PNP bases
    (with V8 = 1.65 V as the static null-test bias). The DACs were never
2026-06-20 kicad(buffer_keyer): MCP4728 re-placed correctly + MCP4921 VREF RC filter + LM7171 bypass note
    - U5 -> U8 MCP4728 deleted and re-placed (no mirror this time); all 10
    pins now wired to the correct nets: VIN/+3.3V, GND, SCL/SDA hier
    labels, LDAC/LDAC_4728, RDY/VC/VD with no-connect flags, VA -> R_INJ2
    -> T2.base, VB -> R_INJ1 -> T1.base. Net tracer confirms.
    - MCP4921 VREF: added R16 (10R series) + C14 (1uF to GND) RC filter on
    pin 6 to reject +5V supply noise from translating directly into DAC
2026-06-20 kicad + qucs: set MCP4921 C13 bulk bypass to 1uF; QUCS keyer.sch edit
    - buffer_keyer.kicad_sch: C13 value set to 1uF (placeholder was the
    symbol library name "C_Polarized"). 1uF + 100nF (Cx1) bypass at
    MCP4921 VDD — sufficient for the chip's ~0.5 mA current draw.
    - xmitter_prj/keyer.sch: QUCS simulation schematic edit.
2026-06-21 kicad: rename VFO_OUT signals to direction-named labels (RAW_RF_*, MOD_RF_*)
    The 14 MHz unmodulated signal between VFO and buffer_keyer was
    labeled "VFO_OUT" on BOTH sheets, which was directionally ambiguous.
    The differential post-modulation outputs of the LM7171 stage were
    also labeled "VFO_OUT+/-", which was wrong — by that point in the
    chain the signal is keyed/modulated, not raw VFO.
    Renames:
2026-06-21 kicad: re-architect I2C bus distribution via STEMMA QT to Si5351 hub
    Move I2C (SDA/SCL) and +3.3V distribution from arduino-sheet-origin to
    vfo-sheet-origin, matching the physical plan: STEMMA QT cable carries
    I2C + 3.3V from Metro to Si5351 breakout (off-schematic), and from the
    Si5351 breakout's 0.1" header the bus is distributed via PCB traces to
    other I2C devices (MCP4728, future MCP23017 for LCD).
    Per-file changes:
